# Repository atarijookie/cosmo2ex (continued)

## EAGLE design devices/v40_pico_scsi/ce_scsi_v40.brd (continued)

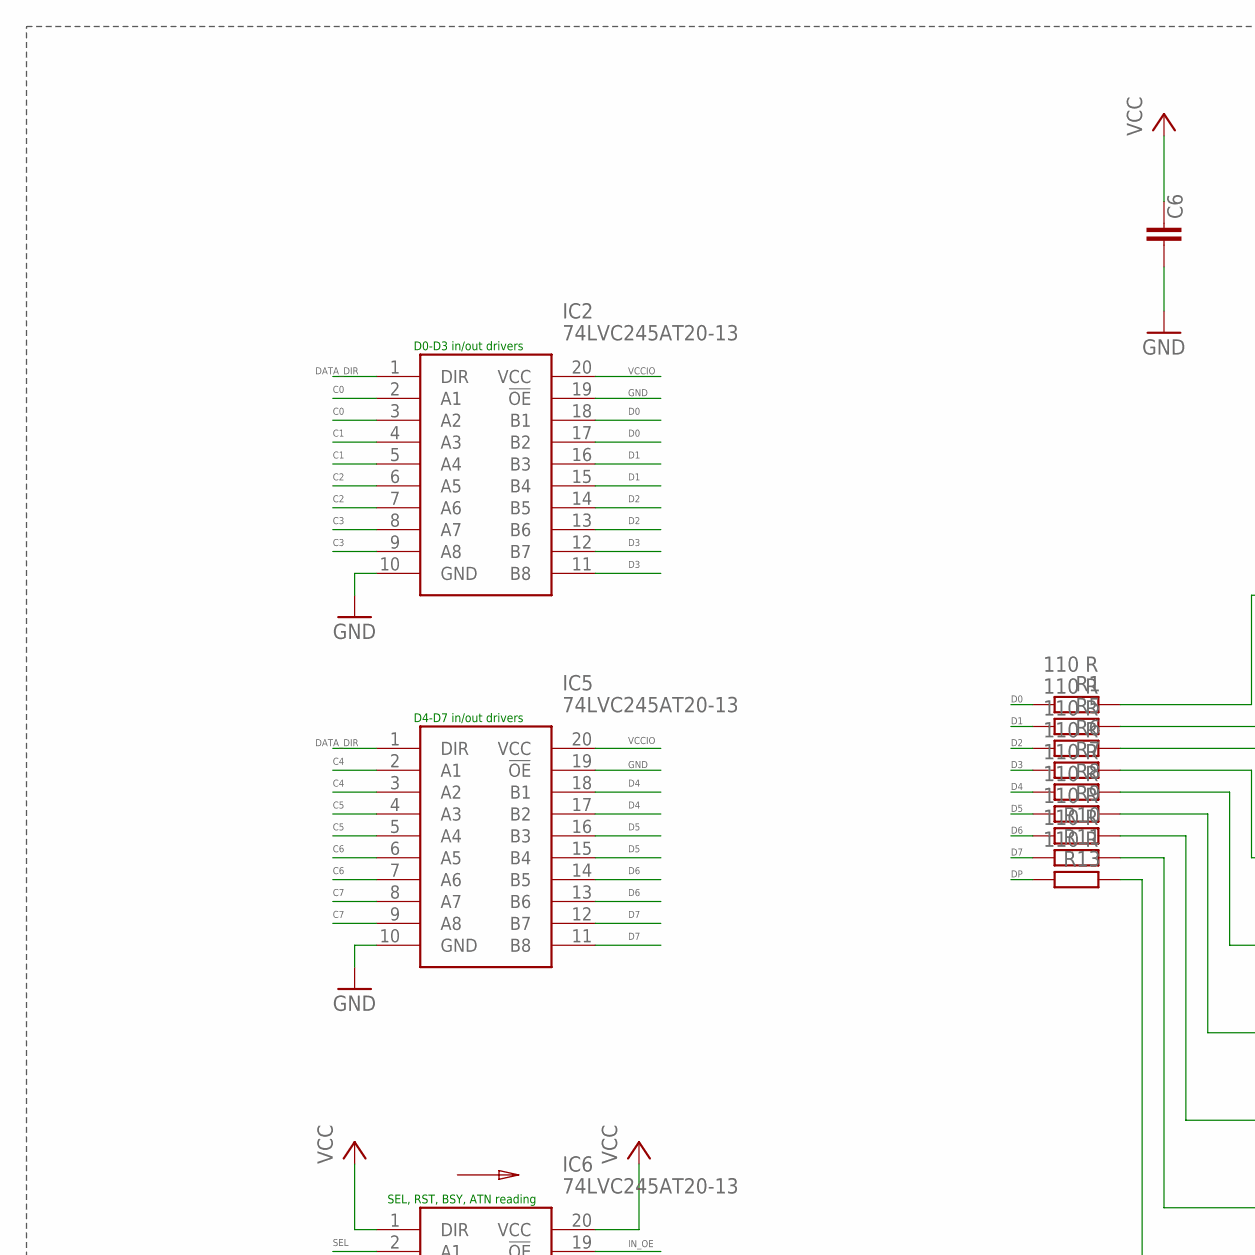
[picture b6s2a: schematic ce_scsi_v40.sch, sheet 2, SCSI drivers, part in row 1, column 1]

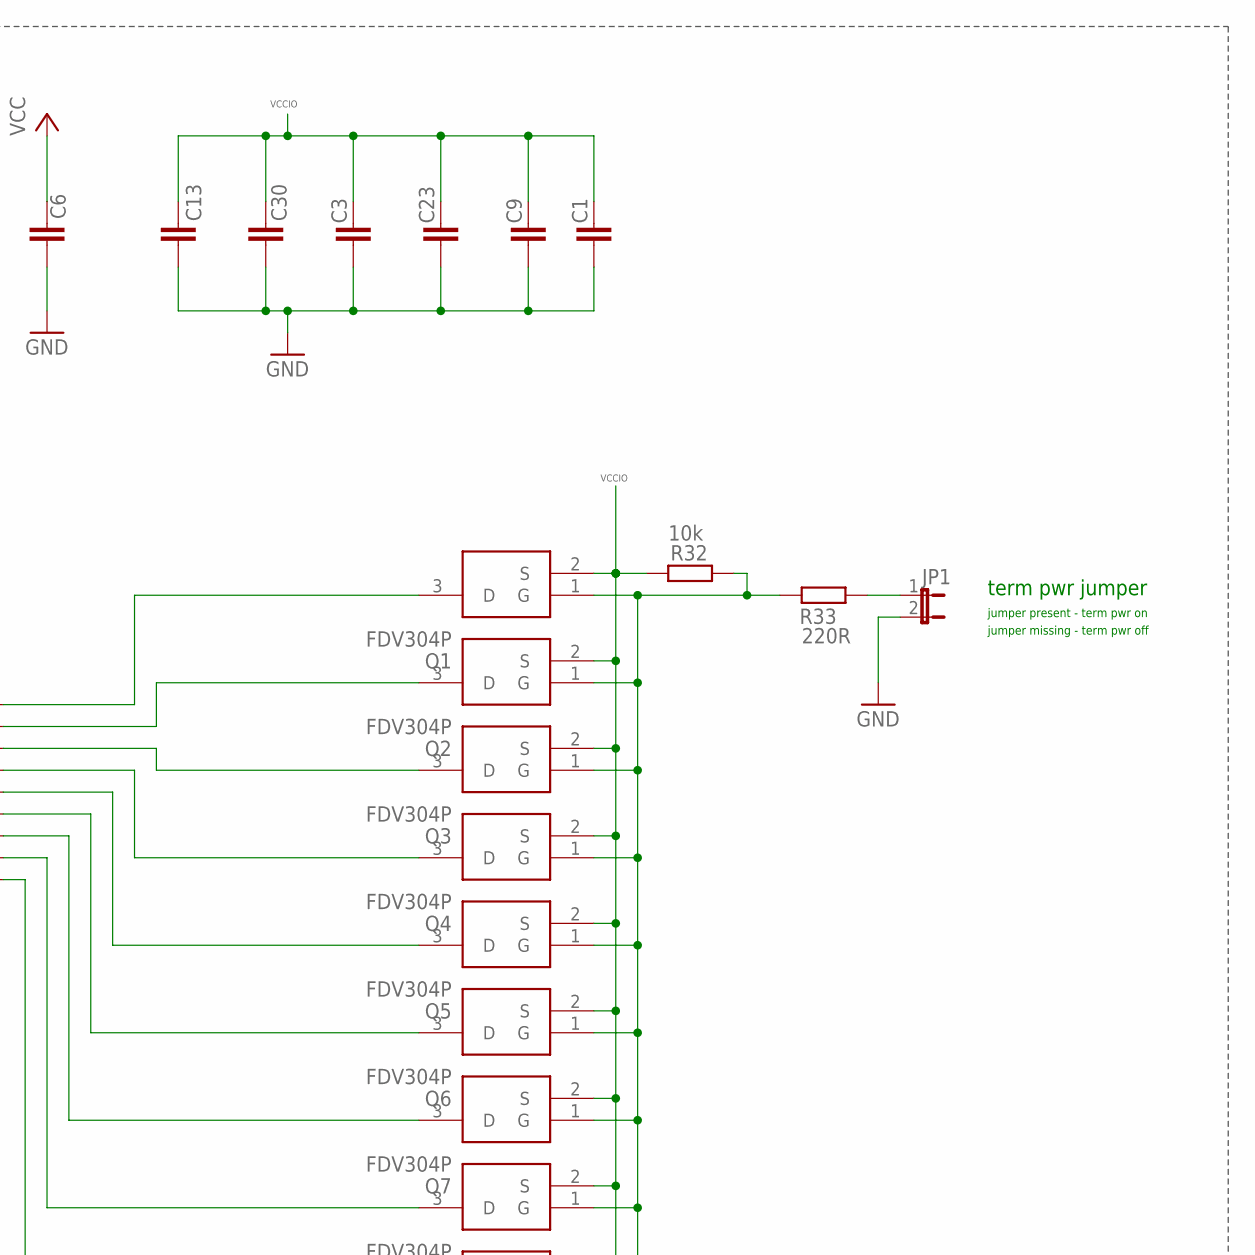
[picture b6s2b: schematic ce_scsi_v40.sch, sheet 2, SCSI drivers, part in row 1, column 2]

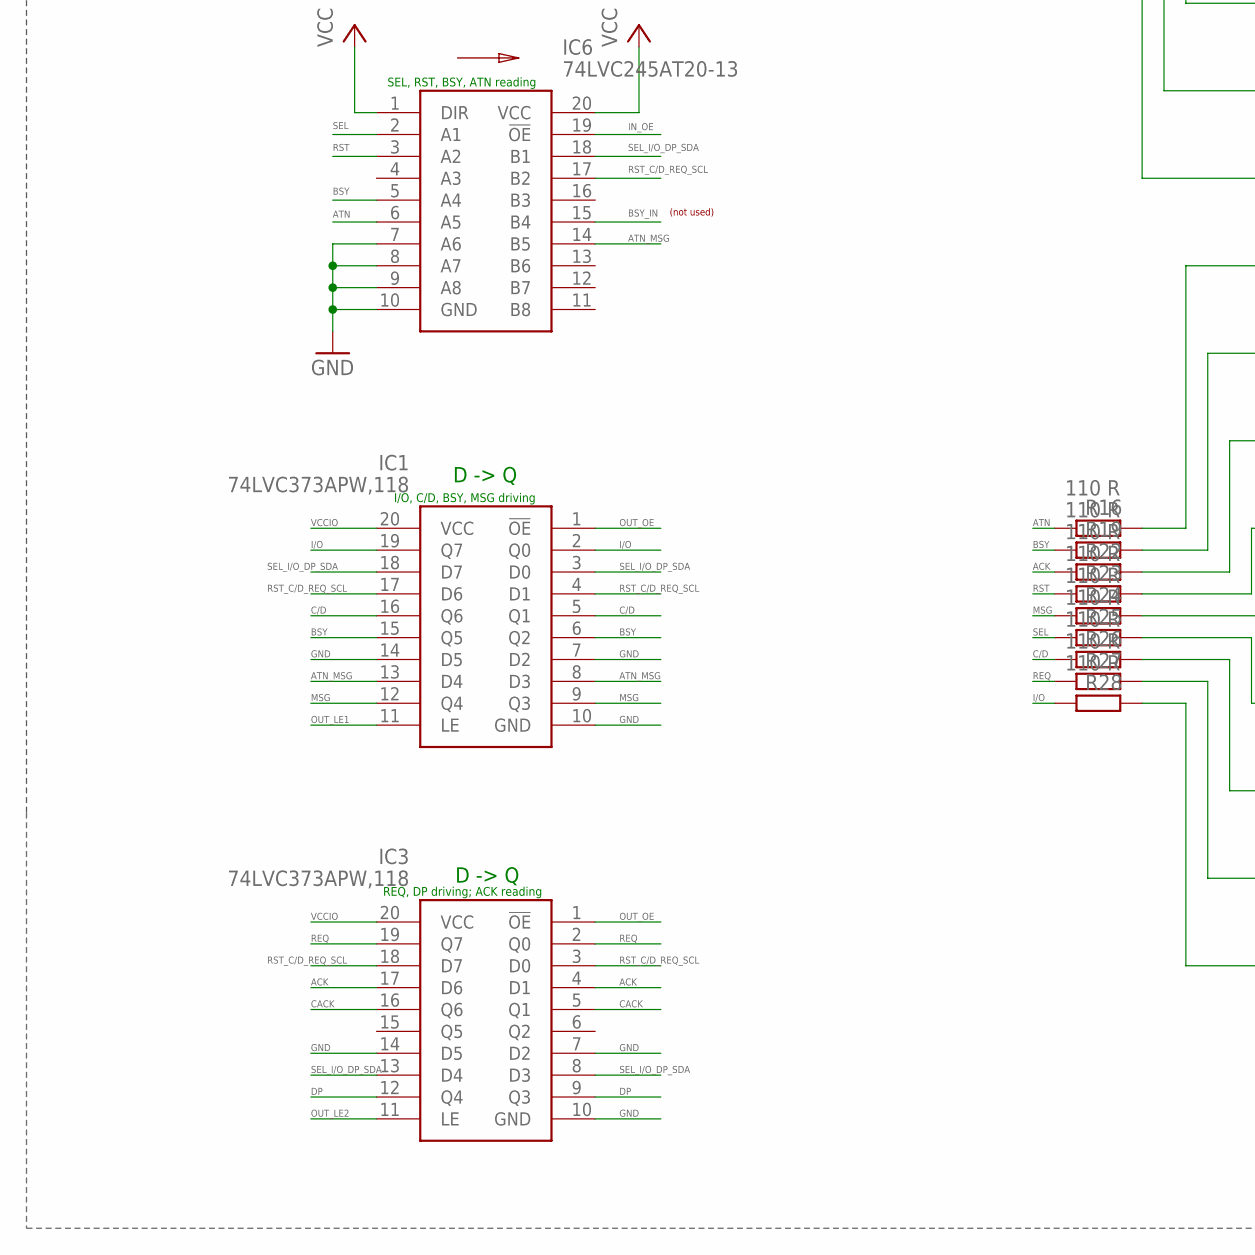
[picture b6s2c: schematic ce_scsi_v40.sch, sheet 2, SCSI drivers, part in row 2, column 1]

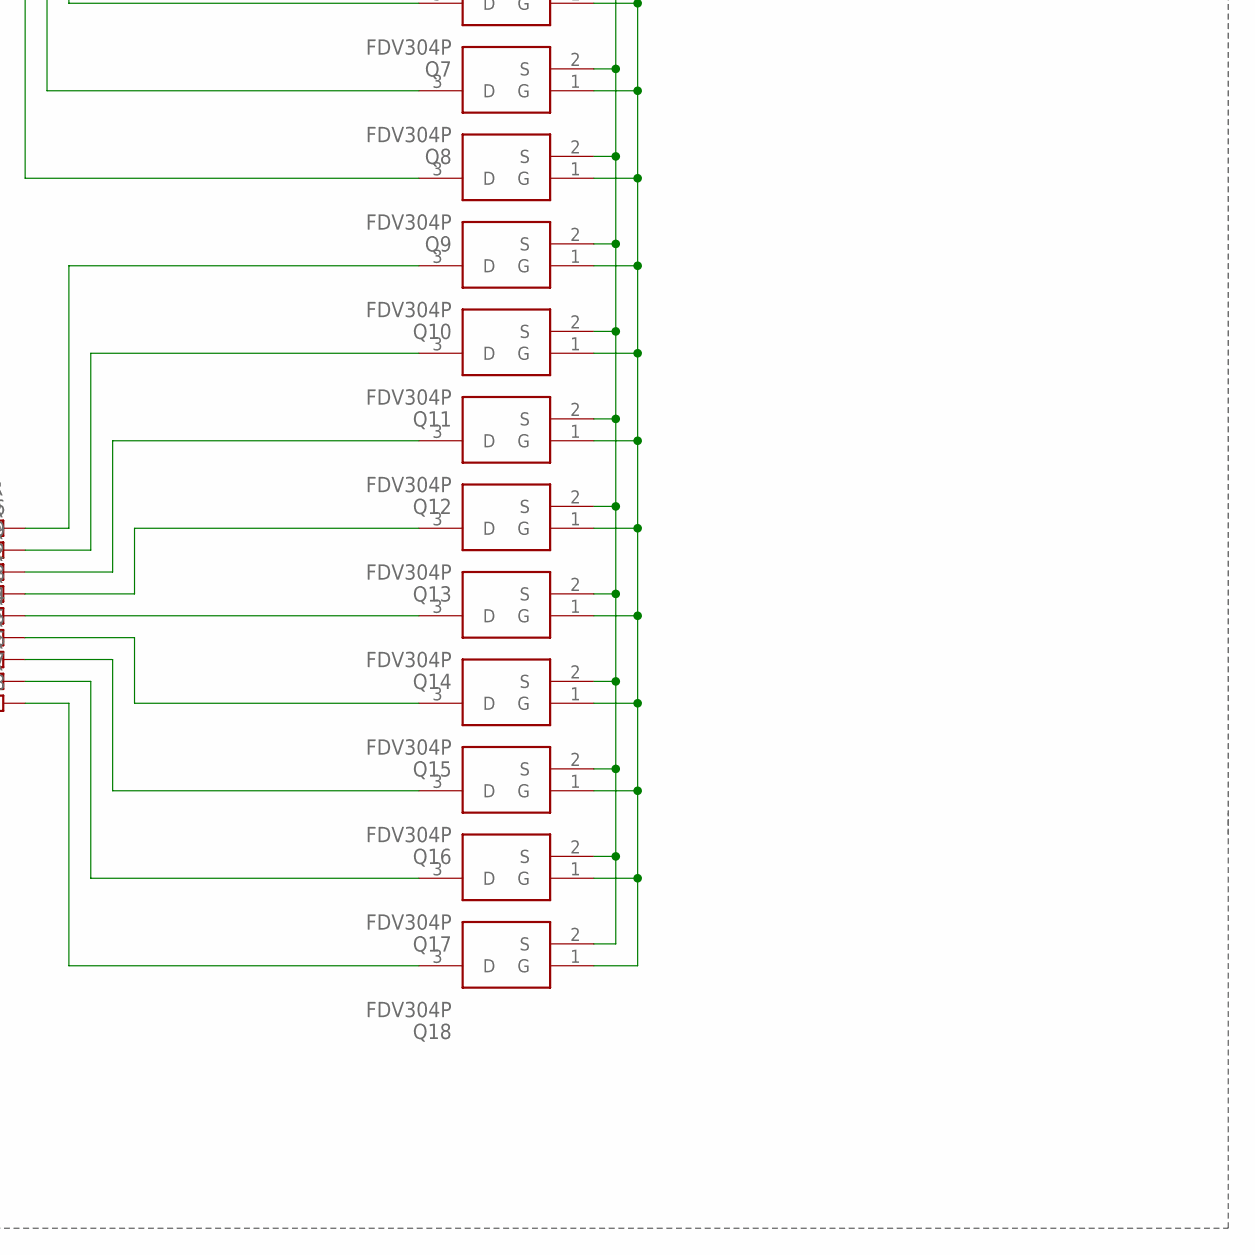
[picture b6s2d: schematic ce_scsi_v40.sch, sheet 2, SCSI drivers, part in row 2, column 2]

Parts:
C1, C3, C6, C9, C13, C23: 100 nF; C0603
C30: 1 uF; C0805
IC1, IC3: 74LVC373APW,118; SOP65P640X110-20N
IC2, IC5, IC6: 74LVC245AT20-13; SOP65P640X120-20N
JP1: JP1E; JP1
Q1, Q2, Q3, Q4, Q5, Q6, Q7, Q8, Q9, Q10, Q11, Q12, Q13, Q14, Q15, Q16, Q17, Q18: FDV304P; SOT95P237X112-3N
R1, R5, R6, R7, R8, R9, R10, R11, R13, R16, R19, R22, R23, R24, R25, R26, R27, R28: 110 R; R0603
R32: 10k; R0603
R33: 220R; R0603

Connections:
AAAA: Q1.3 (D), R1.1
ACK: IC3.4 (D1), IC3.17 (D6), R22.2; also elsewhere on the board
ATN: IC6.6 (A5), R16.2; also elsewhere on the board
ATN_MSG: IC1.8 (D3), IC1.13 (D4), IC6.14 (B5); also elsewhere on the board
BSY: IC1.6 (Q2), IC1.15 (Q5), IC6.5 (A4), R19.2; also elsewhere on the board
BSY_IN: IC6.15 (B4)
C0: IC2.2 (A1), IC2.3 (A2); also elsewhere on the board
C1: IC2.4 (A3), IC2.5 (A4); also elsewhere on the board
C2: IC2.6 (A5), IC2.7 (A6); also elsewhere on the board
C3: IC2.8 (A7), IC2.9 (A8); also elsewhere on the board
C4: IC5.2 (A1), IC5.3 (A2); also elsewhere on the board
C5: IC5.4 (A3), IC5.5 (A4); also elsewhere on the board
C6: IC5.6 (A5), IC5.7 (A6); also elsewhere on the board
C7: IC5.8 (A7), IC5.9 (A8); also elsewhere on the board
C/D: IC1.5 (Q1), IC1.16 (Q6), R26.2; also elsewhere on the board
CACK: IC3.5 (Q1), IC3.16 (Q6); also elsewhere on the board
D0: IC2.17 (B2), IC2.18 (B1), R1.2; also elsewhere on the board
D1: IC2.15 (B4), IC2.16 (B3), R5.2; also elsewhere on the board
D2: IC2.13 (B6), IC2.14 (B5), R6.2; also elsewhere on the board
D3: IC2.11 (B8), IC2.12 (B7), R7.2; also elsewhere on the board
D4: IC5.17 (B2), IC5.18 (B1), R8.2; also elsewhere on the board
D5: IC5.15 (B4), IC5.16 (B3), R9.2; also elsewhere on the board
D6: IC5.13 (B6), IC5.14 (B5), R10.2; also elsewhere on the board
D7: IC5.11 (B8), IC5.12 (B7), R11.2; also elsewhere on the board
DATA_DIR: IC2.1 (DIR), IC5.1 (DIR); also elsewhere on the board
DP: IC3.9 (Q3), IC3.12 (Q4), R13.2; also elsewhere on the board
GND: C1.2, C3.2, C6.2, C9.2, C13.2, C23.2, C30.2, IC1.7 (D2), IC1.10 (GND), IC1.14 (D5), IC2.10 (GND), IC2.19 (!OE), IC3.7 (D2), IC3.10 (GND), IC3.14 (D5), IC5.10 (GND), IC5.19 (!OE), IC6.7 (A6), IC6.8 (A7), IC6.9 (A8), IC6.10 (GND), JP1.2; also elsewhere on the board
I/O: IC1.2 (Q0), IC1.19 (Q7), R28.2; also elsewhere on the board
IN_OE: IC6.19 (!OE); also elsewhere on the board
MSG: IC1.9 (Q3), IC1.12 (Q4), R24.2; also elsewhere on the board
unnamed: JP1.1, R33.2
unnamed: Q2.3 (D), R5.1
unnamed: Q3.3 (D), R6.1
unnamed: Q4.3 (D), R7.1
unnamed: Q5.3 (D), R8.1
unnamed: Q6.3 (D), R9.1
unnamed: Q7.3 (D), R10.1
unnamed: Q8.3 (D), R11.1
unnamed: Q9.3 (D), R13.1
unnamed: Q10.3 (D), R16.1
unnamed: Q11.3 (D), R19.1
unnamed: Q12.3 (D), R22.1
unnamed: Q13.3 (D), R23.1
unnamed: Q14.3 (D), R24.1
unnamed: Q15.3 (D), R25.1
unnamed: Q16.3 (D), R26.1
unnamed: Q17.3 (D), R27.1
unnamed: Q18.3 (D), R28.1
OUT_LE1: IC1.11 (LE); also elsewhere on the board
OUT_LE2: IC3.11 (LE); also elsewhere on the board
OUT_OE: IC1.1 (!OE), IC3.1 (!OE); also elsewhere on the board
REQ: IC3.2 (Q0), IC3.19 (Q7), R27.2; also elsewhere on the board
RST: IC6.3 (A2), R23.2; also elsewhere on the board
RST_C/D_REQ_SCL: IC1.4 (D1), IC1.17 (D6), IC3.3 (D0), IC3.18 (D7), IC6.17 (B2); also elsewhere on the board
SEL: IC6.2 (A1), R25.2; also elsewhere on the board
SEL_I/O_DP_SDA: IC1.3 (D0), IC1.18 (D7), IC3.8 (D3), IC3.13 (D4), IC6.18 (B1); also elsewhere on the board
TP_ON: Q1.1 (G), Q2.1 (G), Q3.1 (G), Q4.1 (G), Q5.1 (G), Q6.1 (G), Q7.1 (G), Q8.1 (G), Q9.1 (G), Q10.1 (G), Q11.1 (G), Q12.1 (G), Q13.1 (G), Q14.1 (G), Q15.1 (G), Q16.1 (G), Q17.1 (G), Q18.1 (G), R32.2, R33.1
VCC: C6.1, IC6.1 (DIR), IC6.20 (VCC); also elsewhere on the board
VCCIO: C1.1, C3.1, C9.1, C13.1, C23.1, C30.1, IC1.20 (VCC), IC2.20 (VCC), IC3.20 (VCC), IC5.20 (VCC), Q1.2 (S), Q2.2 (S), Q3.2 (S), Q4.2 (S), Q5.2 (S), Q6.2 (S), Q7.2 (S), Q8.2 (S), Q9.2 (S), Q10.2 (S), Q11.2 (S), Q12.2 (S), Q13.2 (S), Q14.2 (S), Q15.2 (S), Q16.2 (S), Q17.2 (S), Q18.2 (S), R32.1; also elsewhere on the board

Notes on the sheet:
D -> Q
term pwr jumper
jumper present - term pwr on
jumper missing - term pwr off
D0-D3 in/out drivers
D4-D7 in/out drivers
SEL, RST, BSY, ATN reading
I/O, C/D, BSY, MSG driving
REQ, DP driving; ACK reading
(not used)

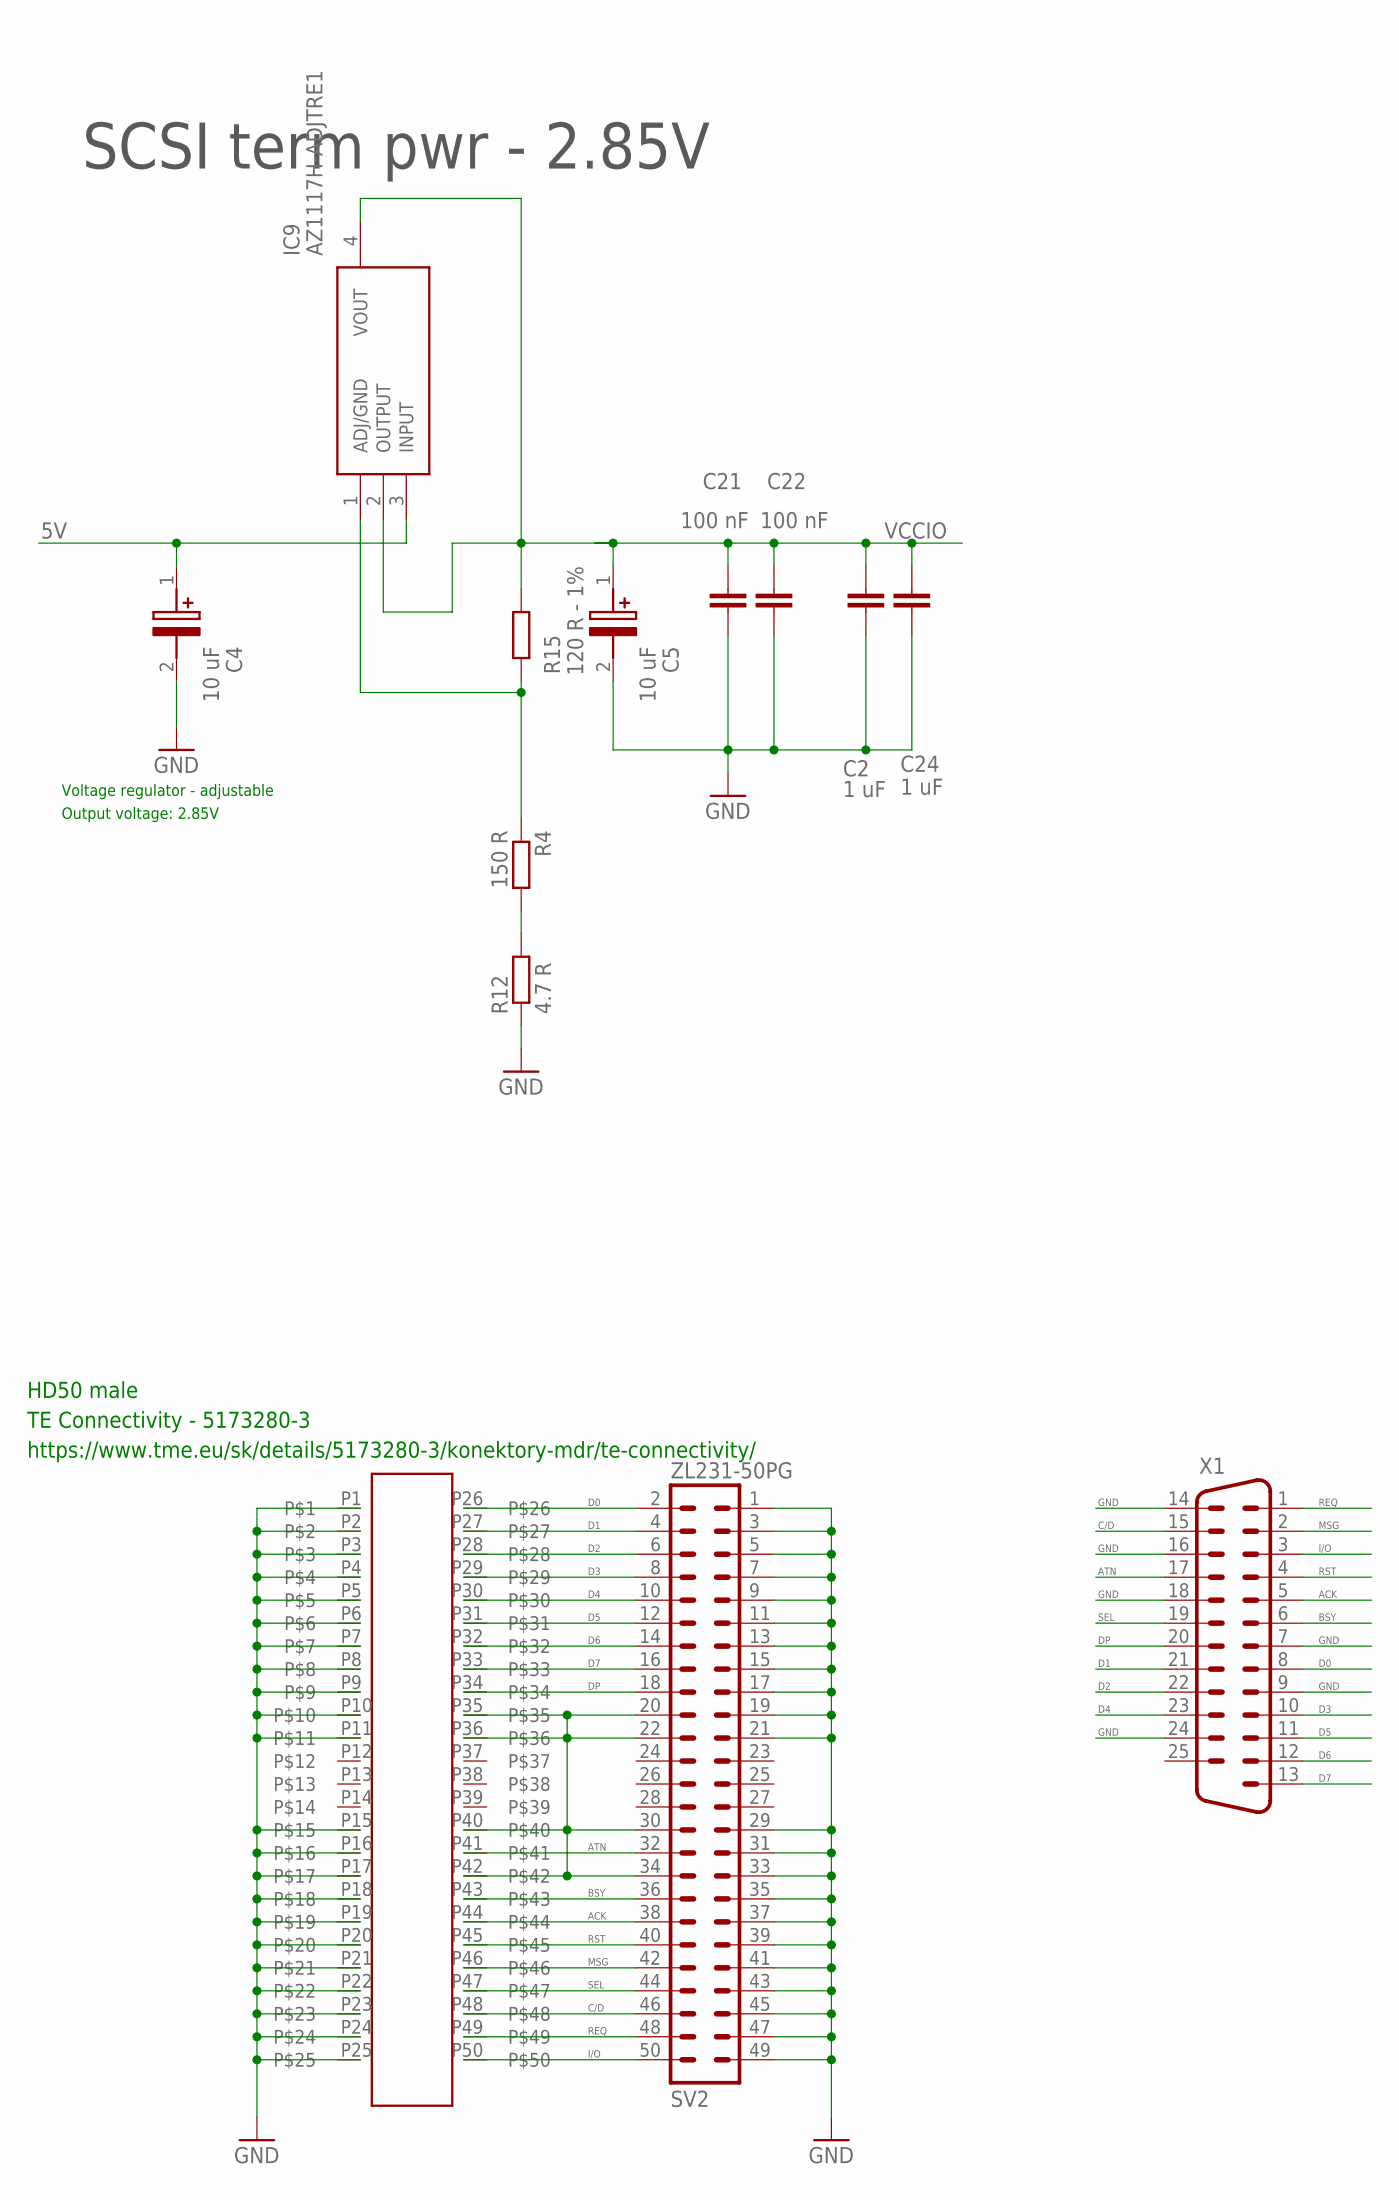
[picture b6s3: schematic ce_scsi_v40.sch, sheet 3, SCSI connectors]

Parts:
C2, C24: 1 uF; C0805
C4, C5: 10 uF; CAPPM3528X210N; MANUFACTURER_PART_NUMBER 293D106X9016B2TE3
C21, C22: 100 nF; C0603
IC9: AZ1117H-ADJTRE1; SOT230P700X185-4N
R4: 150 R; R0603
R12: 4.7 R; R0603
R15: 120 R - 1%; R0603
SV2: ZL231-50PG; ML50
U$2: TE Connectivity - 5173280-3; HD50_MALE
X1: M25V

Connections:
5V: C4.1 (+), IC9.3 (INPUT); also elsewhere on the board
ACK: SV2.38, U$2.P44, X1.5; also elsewhere on the board
ATN: SV2.32, U$2.P41, X1.17; also elsewhere on the board
BSY: SV2.36, U$2.P43, X1.6; also elsewhere on the board
C/D: SV2.46, U$2.P48, X1.15; also elsewhere on the board
D0: SV2.2, U$2.P26, X1.8; also elsewhere on the board
D1: SV2.4, U$2.P27, X1.21; also elsewhere on the board
D2: SV2.6, U$2.P28, X1.22; also elsewhere on the board
D3: SV2.8, U$2.P29, X1.10; also elsewhere on the board
D4: SV2.10, U$2.P30, X1.23; also elsewhere on the board
D5: SV2.12, U$2.P31, X1.11; also elsewhere on the board
D6: SV2.14, U$2.P32, X1.12; also elsewhere on the board
D7: SV2.16, U$2.P33, X1.13; also elsewhere on the board
DP: SV2.18, U$2.P34, X1.20; also elsewhere on the board
GND: C2.2, C4.2 (-), C5.2 (-), C21.2, C22.2, C24.2, R12.1, SV2.1, SV2.3, SV2.5, SV2.7, SV2.9, SV2.11, SV2.13, SV2.15, SV2.17, SV2.19, SV2.20, SV2.21, SV2.22, SV2.29, SV2.30, SV2.31, SV2.33, SV2.34, SV2.35, SV2.37, SV2.39, SV2.41, SV2.43, SV2.45, SV2.47, SV2.49, U$2.P1, U$2.P2, U$2.P3, U$2.P4, U$2.P5, U$2.P6, U$2.P7, U$2.P8, U$2.P9, U$2.P10, U$2.P11, U$2.P15, U$2.P16, U$2.P17, U$2.P18, U$2.P19, U$2.P20, U$2.P21, U$2.P22, U$2.P23, U$2.P24, U$2.P25, U$2.P35, U$2.P36, U$2.P40, U$2.P42, X1.7, X1.9, X1.14, X1.16, X1.18, X1.24; also elsewhere on the board
I/O: SV2.50, U$2.P50, X1.3; also elsewhere on the board
MSG: SV2.42, U$2.P46, X1.2; also elsewhere on the board
unnamed: R4.2, R12.2
unnamed: IC9.1 (ADJ/GND), R4.1, R15.2
REQ: SV2.48, U$2.P49, X1.1; also elsewhere on the board
RST: SV2.40, U$2.P45, X1.4; also elsewhere on the board
SEL: SV2.44, U$2.P47, X1.19; also elsewhere on the board
VCCIO: C2.1, C5.1 (+), C21.1, C22.1, C24.1, IC9.2 (OUTPUT), IC9.4 (VOUT), R15.1; also elsewhere on the board

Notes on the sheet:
Voltage regulator - adjustable
Output voltage: 2.85V
SCSI term pwr - 2.85V
HD50 male
TE Connectivity - 5173280-3
https://www.tme.eu/sk/details/5173280-3/konektory-mdr/te-connectivity/
